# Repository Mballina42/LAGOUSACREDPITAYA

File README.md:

# HARDWARE PARA LAGO USAC CON RED PITAYA
Este proyecto recopila los avances realizados por [Escaramujo Project and LAGO Project matching hardware ](https://github.com/ECFM-USAC/EscaramujoLagoMatch), realizando cambios en el diseño de la PCB.

## Descripción
El diseño busca controlar el voltaje de alimentación para la placa de la base de un PMT Photonix, obteniendo la linea de alimentación principal de la Red Pitaya, a su vez enviar información de temperatura, presión barométrica y GPS. 

Dado a que el tipo de voltaje necesitado por la base del PMT debe de ser lineal, la placa debe de proveer los siguientes voltajes:
* 5 VDC (MAX604)
* 3.3 VDC (MAX603)
* 12 VDC 
* 0 - 5 VDC variable
Esta placa se conecta a la base del PMT por medio de un conector RJ45.

Con base en el pinout de la Red Pitaya se utiliza los *pines IDE extension connector*

La alimentación de la placa se obtiene del pin +5V.

Se utiliza el modulo BMP180 para la medición de presión barométrica y temperatura, conectado a la Red Pitaya por medio un conector RJ11 utilizando el protocolo de comunicación I2C, con los pines: I2C_SDA y I2C_SCL.

Se utiliza el modulo NEO-6M GPS, conectado por medio de HEADERS IDC y hacia la Red Pitaya por medio de UART_RX, UART_TX y DIO1_N.

Para el control del voltaje se utilizan los pines SPI_CS, SPI_CLK y SPI_MOSI.

[Este es el esquemático del proyecto en formato pdf](Imagenes/esquematico.pdf), también pueden consultarse los editables en la carpeta HARDWARE.

## Resultado final
El diseño del circuito y la PCB se realizaron en el software KiCad. Se muestra el modelo final de la PBC.

Dentro de la carpeta Gerber, se encuentra el gerber de cada parte del PCB y dentro de la carpeta CNC_code se encuentra el código para CNC elaborado en el software **FlatCAM**.

## License

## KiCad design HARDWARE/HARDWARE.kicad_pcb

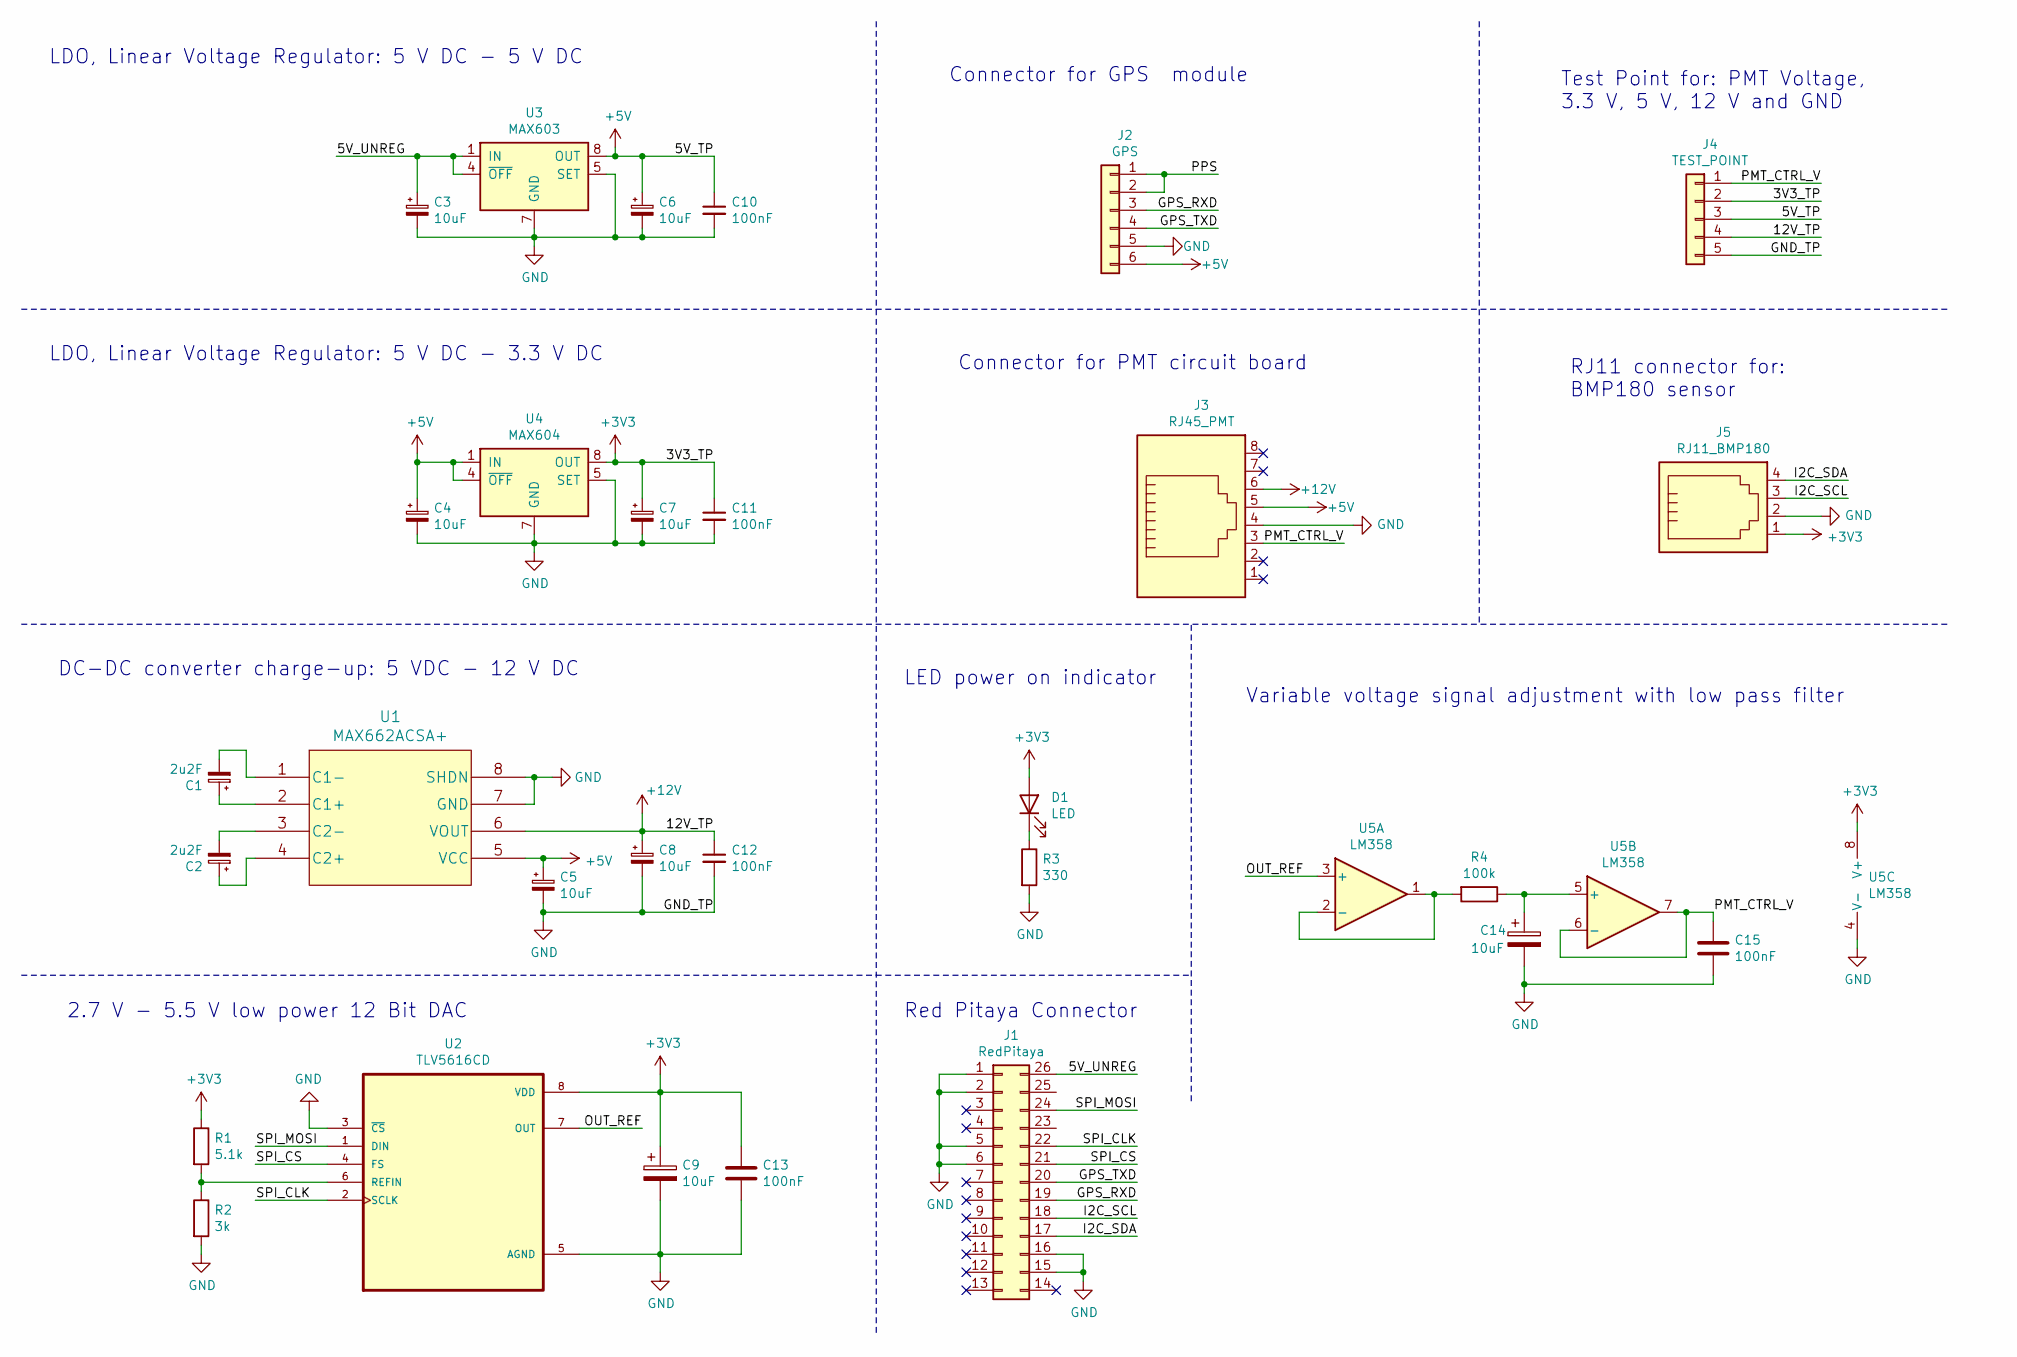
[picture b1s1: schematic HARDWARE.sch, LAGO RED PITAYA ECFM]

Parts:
C1, C2: 2u2F; CP_Radial_Tantal_D4.5mm_P2.50mm
C3, C4, C5, C6, C7, C8, C9, C14: 10uF; CP_Radial_Tantal_D4.5mm_P2.50mm
C10, C11, C12, C13, C15: 100nF; C_0805_2012Metric
D1: LED; R_0603_1608Metric
J1: RedPitaya; IDC-Header_2x13_P2.54mm_Vertical
J2: GPS; PinSocket_1x06_P2.54mm_Vertical
J3: RJ45_PMT; RJ45_Amphenol_54602-x08_Horizontal
J4: TEST_POINT; PinHeader_1x05_P2.54mm_Vertical
J5: RJ11_BMP180; RJ14_Connfly_DS1133-S4_Horizontal
R1: 5.1k; R_0603_1608Metric
R2: 3k; R_0603_1608Metric
R3: 330; R_0603_1608Metric
R4: 100k; R_0603_1608Metric
U1: MAX662ACSA+; MAX662ACSA&plus_
U2: TLV5616CD; SOIC127P599X175-8N
U3: MAX603; DIP-8_W7.62mm
U4: MAX604; DIP-8_W7.62mm
U5: LM358; SOIC-8_3.9x4.9mm_P1.27mm

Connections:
+3V3: C7.1, C9.1, C11.1, C13.1, D1.2 (A), J4.2, J5.1, R1.1, U2.8 (VDD), U4.8 (OUT), U5.8 (V+)
+5V: C4.1, C5.1, C6.1, C10.1, J2.6, J3.5, J4.3, U1.5 (VCC), U3.8 (OUT), U4.1 (IN), U4.4 (~OFF)
+12V: C8.1, C12.1, J3.6, J4.4, U1.6 (VOUT)
/5V_UNREG: C3.1, J1.26, U3.1 (IN), U3.4 (~OFF)
/GPS_RXD: J1.19, J2.3
/GPS_TXD: J1.20, J2.4
/I2C_SCL: J1.18, J5.3
/I2C_SDA: J1.17, J5.4
/OUT_REF: U2.7 (OUT), U5.3 (+)
/PMT_CTRL_V: C15.1, J3.3, J4.1, U5.6 (-), U5.7
/PPS: J2.1, J2.2
/SPI_CLK: J1.22, U2.2 (SCLK)
/SPI_CS: J1.21, U2.4 (FS)
/SPI_MOSI: J1.24, U2.1 (DIN)
GND: C3.2, C4.2, C5.2, C6.2, C7.2, C8.2, C9.2, C10.2, C11.2, C12.2, C13.2, C14.2, C15.2, J1.1, J1.2, J1.5, J1.6, J1.15, J1.16, J2.5, J3.4, J4.5, J5.2, R2.2, R3.2, U1.7 (GND), U1.8 (SHDN), U2.3 (~CS), U2.5 (AGND), U3.2 (GND), U3.3 (GND), U3.5 (SET), U3.6 (GND), U3.7 (GND), U4.2 (GND), U4.3 (GND), U4.5 (SET), U4.6 (GND), U4.7 (GND), U5.4 (V-)
unnamed: C1.1, U1.2 (C1+)
unnamed: C1.2, U1.1 (C1-)
unnamed: C2.1, U1.4 (C2+)
unnamed: C2.2, U1.3 (C2-)
unnamed: C14.1, R4.1, U5.5 (+)
unnamed: D1.1 (K), R3.1
unnamed: R1.2, R2.1, U2.6 (REFIN)
unnamed: R4.2, U5.1, U5.2 (-)

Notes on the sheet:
LDO, Linear Voltage Regulator: 5 V DC - 5 V DC
LDO, Linear Voltage Regulator: 5 V DC - 3.3 V DC
DC-DC converter charge-up: 5 VDC - 12 V DC
2.7 V - 5.5 V low power 12 Bit DAC
Connector for GPS module
Test Point for: PMT Voltage, 3.3 V, 5 V, 12 V and GND
Variable voltage signal adjustment with low pass filter
LED power on indicator
Red Pitaya Connector
Connector for PMT circuit board
RJ11 connector for: BMP180 sensor

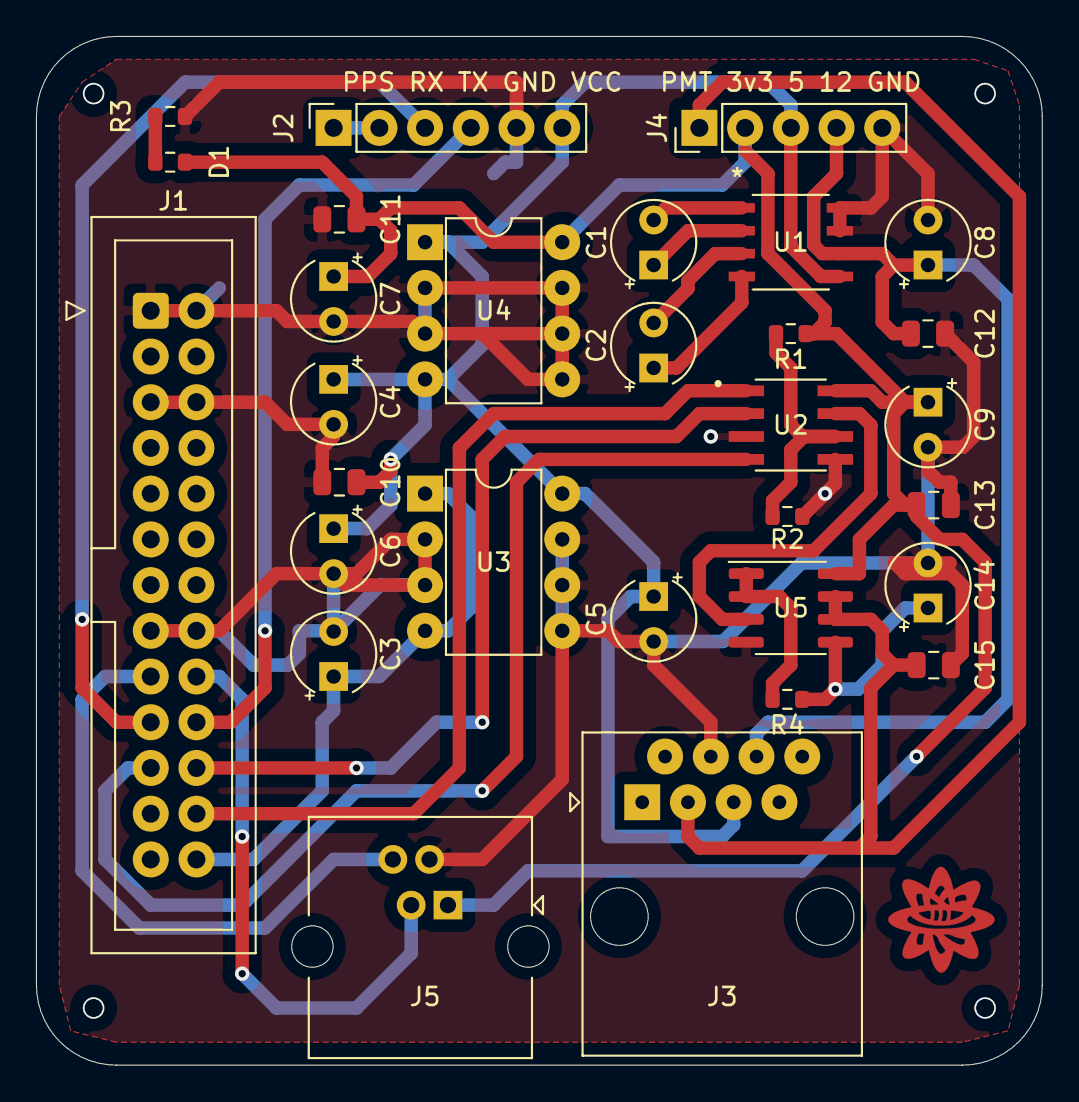
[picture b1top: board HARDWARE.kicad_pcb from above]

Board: 2 copper layers, 55.9 x 57.1 mm, 30 parts (0 on the bottom side), 23 nets.

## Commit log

2021-07-09 09/07/2021
2021-07-09 09/07/21.2
2021-07-09 9/7/21.3
2021-07-09 9/7/21.4
2021-07-09 9/7/21.5
2021-07-14 13/07/2021
2021-07-14 14/07/2021

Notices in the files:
README.md:
License:
[License: MIT](MIT-LICENSE.txt)
